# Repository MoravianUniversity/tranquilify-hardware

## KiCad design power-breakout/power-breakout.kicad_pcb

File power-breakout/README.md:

# Power Breakout

Battery + USB-C power path breakout for Tranquilify. Supplies switched **+3.3 V** to an ESP32-P4 (and onboard C6), two ADAU1787 codec boards, with charge-while-off, ship mode, and I2C fuel gauging.

Schematic-first; PCB later. Target assembly: JLCPCB.

## Role in the system

| Consumer | Rail | Notes |
|----------|------|--------|
| ESP32-P4 + ESP32-C6 | `+3V3` (switched) | Soft power via buck EN / host `HOST_3V3_EN` |
| 2× ADAU1787 breakouts | `+3V3` | Codecs make their own 1.8 V on-board |
| STC3115 fuel gauge | Battery (always) | Low-side sense; I2C @ 0x38 on host bus |
| Soft-power + charger | Always-on from `SYS` / pack | Charge LED works while “off”; soft-power is off-board via J6 |

## Locked requirements

- **USB-C** 5 V sink only; **USB HS** D+/D− shared with charger BC1.2 via DSEL mux
- **Power path:** system runs from USB with empty or **missing** battery
- **Battery:** ~3500 mAh 1S Li-ion target (was Adafruit 353 6600 mAh), JST-PH, pack PCM, **no NTC**
- Charge ~**1 A** (pack max 1.5 A; ICHG in firmware + ILIM pin)
- Soft power = **Mode B** (cut system load / Waveshare 3V3_EN); path toward deep-sleep later
- Soft-power UX (hold-to-on, no auto-on on plug-in, click/hold to host) is **off-board** on **J6 SPWR** — not populated on this rev
- Critical-battery auto-off via gauge + firmware (once soft-power can cut `BUCK_EN`)
- Ship mode via BQ25895 `BATFET_DIS` / `/QON` wake
- Connectors: JST-PH battery; JST-GH for power, control, USB data; 1.27 mm header for soft-power experiments

## Architecture

```
USB-C VBUS ──► BQ25895 (power path, ~1 A charge)
                 │
    D+/D− ──► FSUSB42 (DSEL) ──┬── CHG_DP/DN → BQ25895 BC1.2
                               └── HOST_DP/DN → J2 USB header
                 │
    PACK+ ◄──────┤◄── JST-PH pin1; charger BAT = PACK+
                 │
                SYS
                 │
   ┌─────────────┼──────────────────┐
   │             │                  │
always-on   R16 100k ↑ EN      STAT → CHG LED
(SYS)            │
                 ▼
         TPS62823 EN → +3V3 → P4 / C6 / codecs
                 │
         J1 POWER: GND / HOST_3V3_EN (OD) / +3V3

    PACK- (JST-PH pin2) ── 10 mΩ R9 ──► GND   (STC3115 CG/GND Kelvin)

J6 SPWR: SYS / GND / BTN / BUCK_EN
  BTN also → BQ25895 /QON (ship wake)
  Empty header ⇒ EN pulled up ⇒ +3V3 default on when SYS is up
STC3115 low-side sense on PACK-, I2C @ 0x38 (host bus, not codec bus)
```

RGB indicator lives on the eventual main board, not this power breakout.

**Dropped vs earlier draft:** no LM66200 / `AUX_5V` input OR. USB-C is the only VBUS source into the charger. On-board **MAX16150** soft-power IC removed in favor of **J6 SPWR** (see below).

### Soft power vs ship mode

| State | What happens |
|-------|----------------|
| **Default (no SPWR board)** | `BUCK_EN` pulled to `SYS` via R16 → `+3V3` on whenever `SYS` exists (USB and/or battery). |
| **User off (with SPWR daughter)** | Daughter deasserts `BUCK_EN` → `+3V3` down. Charger + gauge live. USB can still charge. |
| **Ship** | Host I2C → BQ25895 `BATFET_DIS`; BATFET off; ~µA. Exit: long `/QON` (BTN to GND) or USB plug. |
| **Deep sleep (later)** | Keep `+3V3` up; P4 sleep — optional future |

### Soft-power experiment port (J6 SPWR)

No on-board pushbutton controller. **J6** (1×4, 1.27 mm) exposes the always-on domain so you can try options without a power-board respin:

| Pin | Net | Contract |
|-----|-----|----------|
| 1 | `SYS` | Always-on supply for a soft-power circuit |
| 2 | `GND` | Ground |
| 3 | `BTN` | Active-low button node; also tied to BQ25895 `/QON` |
| 4 | `BUCK_EN` | TPS62823 `EN` (active high). Weak **100 kΩ** pull-up to `SYS` (R16) for default-on |

**Suggested implementations on J6**

- **MAX16150** (or similar): VCC=`SYS`, PB_IN=`BTN`, OUT→`BUCK_EN`, CLR/INT to the host as needed (host wires are no longer on J3).
- **Simpler:** discrete latch / open-drain MOSFET from a GPIO daughterboard; OD **low** on `BUCK_EN` for off.
- **Bring-up:** leave J6 open — rail stays on; short `BTN`–`GND` only if testing `/QON` / ship wake.

Product UX (hold-to-on, no auto-on on plug-in, click vs hold) lives entirely on whatever you plug into SPWR (+ host wiring you add).

### Dev board (Waveshare ESP32-P4-WIFI6)

| Mode | Intent |
|------|--------|
| **B – Rail / 3V3_EN** | Feed Waveshare from `+3V3`; `HOST_3V3_EN` OD-low while breakout `SYS` is present (disables module regulator when breakout is powering the rail). |
| USB data | Host USB via J2 (`HOST_DP`/`HOST_DN`); pin 1 V left N/C. DSEL mux hands D+/D− to host after BC1.2. |

## Major parts (schematic)

| Ref | Part | Why |
|-----|------|-----|
| U1 | **BQ25895RTW** | Switch-mode power-path charger, ship (`BATFET_DIS`), `/QON` wake, `STAT` LED, DSEL, I2C; ICHG ~1 A in firmware |
| U3 | **STC3115AIQT** | OptimGauge mixed mode; ~3500 mAh; low-side 10 mΩ; LCSC C2688637. `ALM`→`BAT_ALM` (RN1 pull-up); `RSTIO`→GND (feature off); `BATD` 1 kΩ→GND; VIN filter R11+C16; VCC C10 1 µF |
| U4 | **TPS62823DLC** | 3 A buck, VIN down to 2.4 V → `+3V3`; `EN` default-on via R16 |
| U5 | **USBLC6-2SC6** | USB ESD on `USB_DP`/`USB_DN` |
| U6 | **FSUSB42MUX** | DSEL mux: BC1.2 (HSD1) vs host USB (HSD2); OE# grounded; VCC from `SYS` |
| R16 | **100 kΩ** | `SYS` → `BUCK_EN` pull-up (default on) |
| D1 | LED + R from `STAT` | Charge LED while system off |
| J1 | JST-GH 3 POWER | `GND` / `HOST_3V3_EN` / `+3V3` |
| J2 | JST-GH 4 USB_HDR | USB data header: V N/C, D−, D+, GND |
| J3 | JST-GH 5 CONTROL | I2C + `CHG_INT` + `BAT_ALM` |
| J4 | USB-C + 5.1 kΩ CC | 5 V sink; D+/D− to ESD + mux |
| J5 | JST-PH 2-pin BAT | Battery (`PACK+` / `PACK-`) |
| J6 | 1×4 1.27 mm SPWR | Soft-power experiment: `SYS` / `GND` / `BTN` / `BUCK_EN` |

**FW notes:** clear `MAXC_EN` + `HVDCP_EN` so DSEL releases after BC1.2; set ICHG/VREG; disable or pet charger WDT.

## Datasheets

Saved under `../datasheets/`:

| File | Part |
|------|------|
| `BQ25895_datasheet.pdf` | Charger |
| `BQ25628_datasheet.pdf` | Alternate charger (no D+/D−; not used) |
| `MAX16150_datasheet.pdf` | Soft-power pushbutton IC (optional on J6; not on board) |
| `STC3115_datasheet.pdf` | Fuel gauge (STC3115AIQT) |
| `AN4324_STC3115_system_integration.pdf` | STC3115 integration (if present) |
| `TPS62823_datasheet.pdf` | 3.3 V buck |
| `LM66200_datasheet.pdf` | Dual ideal diode (not used on this rev) |
| `LM66100_datasheet.pdf` | Prior single ideal diode (not used) |
| `ESP32-P4-WIFI6-datasheet.pdf` | Waveshare host module |

## Host connectors

### J1 POWER (JST GH-3)

| Pin | Net | Notes |
|-----|-----|--------|
| 1 | `GND` | |
| 2 | `HOST_3V3_EN` | OD low while `SYS` present; floats when breakout unpowered |
| 3 | `+3V3` | Switched 3.3 V out |

### J2 USB_HDR (JST GH-4)

| Pin | Net | Notes |
|-----|-----|--------|
| 1 | — | V left N/C (host supplies USB VBUS separately if needed) |
| 2 | `HOST_DN` | From mux HSD2 |
| 3 | `HOST_DP` | |
| 4 | `GND` | |

### J3 CONTROL (JST GH-5)

| Pin | Net | Notes |
|-----|-----|--------|
| 1 | `GND` | |
| 2 | `SCL` | 3.3 V I2C (charger `0x6A`; gauge **0x38**) |
| 3 | `SDA` | |
| 4 | `CHG_INT` | BQ25895 `/INT` (OD; RN1 10 kΩ to `+3V3`) |
| 5 | `BAT_ALM` | STC3115 `ALM` (OD; RN1 10 kΩ to `+3V3`) |

### J6 SPWR (1×4, 1.27 mm)

| Pin | Net | Notes |
|-----|-----|--------|
| 1 | `SYS` | Always-on |
| 2 | `GND` | |
| 3 | `BTN` | Shared with `/QON` |
| 4 | `BUCK_EN` | Active-high enable; pulled up on board |

Also: `J4` USB-C, `J5` battery (PH, pin1=`PACK+`, pin2=`PACK-` via R9 to GND).

Host wiring detail: `HOST-SETUP.md`.

## Non-goals (this board)

- Codec 1.8 V generation (on ADAU1787 breakouts)
- RGB LED (on eventual main board)
- On-board soft-power IC / dedicated button jack (use J6)
- Battery NTC (pack has none; TS biased for “OK”)
- AUX 5 V input / ideal-diode OR (dropped this rev)

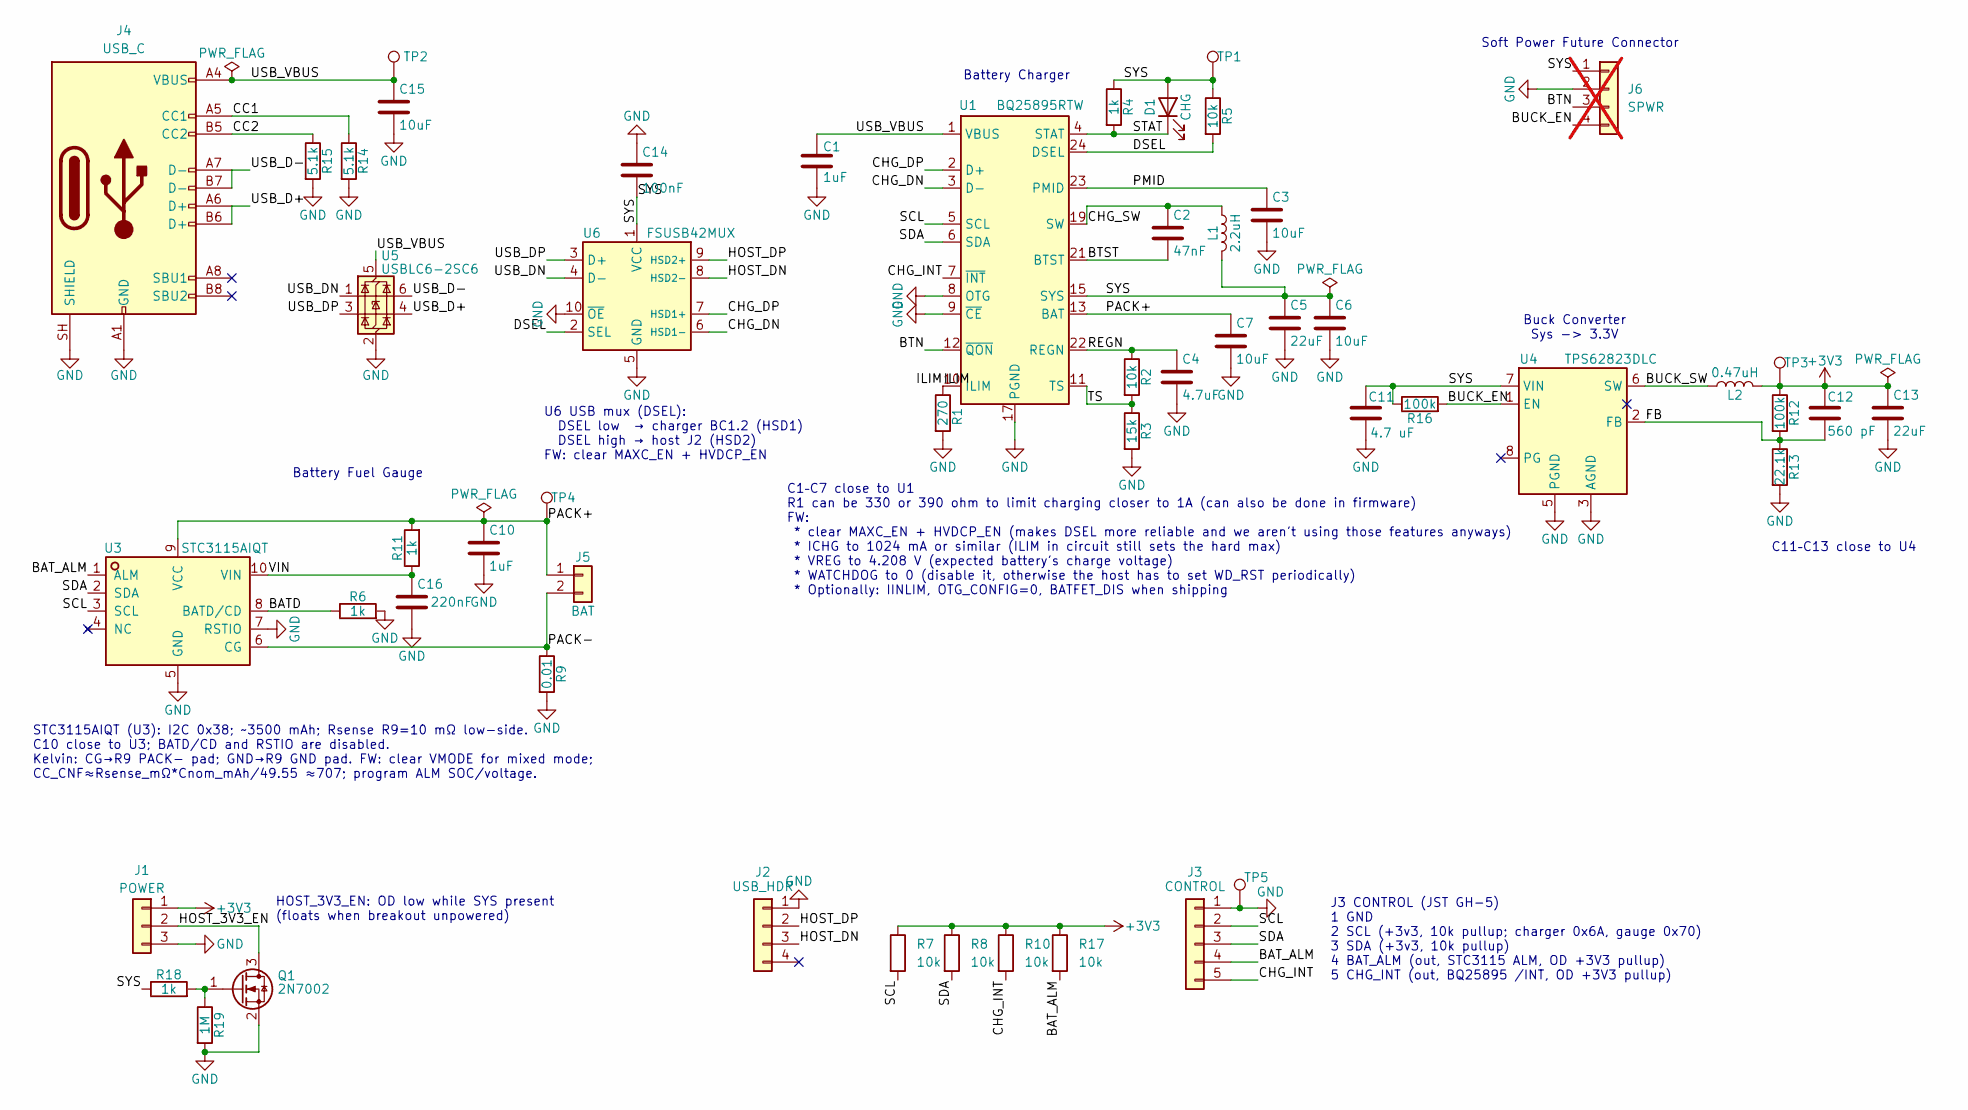
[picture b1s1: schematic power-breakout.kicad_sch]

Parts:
C1: 1uF; C_0402_1005Metric; JLCPCB Item # C49210445
C2: 47nF; C_0402_1005Metric; JLCPCB Item # C272875
C3, C6, C7: 10uF; C_0805_2012Metric; JLCPCB Item # C95841
C4: 4.7uF; C_0603_1608Metric; JLCPCB Item # C19666
C5: 22uF; C_1206_3216Metric; JLCPCB Item # C5252682
C10: 1uF; C_0603_1608Metric; JLCPCB Item # C95843
C11: 4.7 uF; C_0603_1608Metric; JLCPCB Item # C18185770
C12: 560 pF; C_0603_1608Metric; JLCPCB Item # C107054
C13: 22uF; C_0805_2012Metric; JLCPCB Item # C53133025
C14: 100nF; C_0603_1608Metric; JLCPCB Item # C36911391
C15: 10uF; C_1206_3216Metric; JLCPCB Item # C14860
C16: 220nF; C_0603_1608Metric; JLCPCB Item # C1595
D1: CHG; LED_0603_1608Metric; JLCPCB Item # C2892759
J1: POWER; JST_GH_SM03B-GHS-TB_1x03-1MP_P1.25mm_Horizontal; JLCPCB Item # C514175
J2: USB_HDR; JST_GH_SM04B-GHS-TB_1x04-1MP_P1.25mm_Horizontal; JLCPCB Item # C189895
J3: CONTROL; JST_GH_SM05B-GHS-TB_1x05-1MP_P1.25mm_Horizontal; JLCPCB Item # C189896
J4: USB_C; USB_C_Receptacle_HRO_TYPE-C-31-M-12; JLCPCB Item # C165948
J5: BAT; JST_PH_B2B-PH-K_1x02_P2.00mm_Vertical; JLCPCB Item # C131337
J6: SPWR; PinHeader_1x04_P1.27mm_Vertical; not fitted
L1: 2.2uH; L_1008_2520Metric; JLCPCB Item # C1017131
L2: 0.47uH; L_1008_2520Metric; JLCPCB Item # C24296304
Q1: 2N7002; SOT-23; JLCPCB Item # C8545
R1: 270; R_0603_1608Metric; JLCPCB Item # C22966
R2, R5: 10k; R_0603_1608Metric; JLCPCB Item # C25804
R3: 15k; R_0603_1608Metric; JLCPCB Item # C22809
R4, R6, R11, R18: 1k; R_0603_1608Metric; JLCPCB Item # C21190
R7, R8, R10, R17: 10k; R_0402_1005Metric; JLCPCB Item # C25744
R9: 0.01; R_1206_3216Metric; JLCPCB Item # C7467248
R12: 100k; R_0603_1608Metric; JLCPCB Item # C25803
R13: 22.1k; R_0603_1608Metric; JLCPCB Item # C137768
R14, R15: 5.1k; R_0603_1608Metric; JLCPCB Item # C23186
R16: 100k; R_0402_1005Metric; JLCPCB Item # C25741
R19: 1M; R_0603_1608Metric; JLCPCB Item # C22935
TP1, TP2, TP3, TP4, TP5: TestPoint; TestPoint_Pad_D1.0mm
U1: BQ25895RTW; Texas_RTW_WQFN-24-1EP_4x4mm_P0.5mm_EP2.7x2.7mm_ThermalVias; JLCPCB Item # C80200
U3: STC3115AIQT; ST_UFDFPN-10_2x3mm_P0.5mm; JLCPCB Item # C2688637
U4: TPS62823DLC; Texas_VSON-HR-8_1.5x2mm_P0.5mm; JLCPCB Item # C2693497
U5: USBLC6-2SC6; SOT-23-6; JLCPCB Item # C2827654
U6: FSUSB42MUX; MSOP-10_3x3mm_P0.5mm; JLCPCB Item # C11355

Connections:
+3V3: C12.1, C13.1, J1.1, L2.2, R7.1, R8.1, R10.1, R12.1, R17.1, TP3.1 (1_1)
/BATD: R6.1, U3.8 (BATD/CD)
/BAT_ALM: J3.4, R17.2, U3.1 (ALM)
/BTN: J6.3, U1.12 (~QON)
/BTST: C2.2, U1.21 (BTST)
/BUCK_EN: J6.4, R16.2, U4.1 (EN)
/BUCK_SW: L2.1, U4.6 (SW)
/CC1: J4.A5 (CC1), R14.1
/CC2: J4.B5 (CC2), R15.1
/CHG_DN: U1.3 (D-), U6.6 (HSD1-)
/CHG_DP: U1.2 (D+), U6.7 (HSD1+)
/CHG_INT: J3.5, R10.2, U1.7 (~INT)
/CHG_SW: C2.1, L1.1, U1.19 (SW), U1.20 (SW)
/DSEL: R5.2, U1.24 (DSEL), U6.2 (SEL)
/FB: C12.2, R12.2, R13.1, U4.2 (FB)
/HOST_3V3_EN: J1.2, Q1.3 (D)
/HOST_DN: J2.3, U6.8 (HSD2-)
/HOST_DP: J2.2, U6.9 (HSD2+)
/ILIM: R1.1, U1.10 (ILIM)
/PACK+: C7.1, C10.1, J5.1, R11.2, TP4.1 (1_1), U1.13 (BAT), U1.14 (BAT), U3.9 (VCC)
/PACK-: J5.2, R9.1, U3.6 (CG)
/PMID: C3.1, U1.23 (PMID)
/REGN: C4.1, R2.1, U1.22 (REGN)
/SCL: J3.2, R7.2, U1.5 (SCL), U3.3 (SCL)
/SDA: J3.3, R8.2, U1.6 (SDA), U3.2 (SDA)
/STAT: D1.1 (K), R4.2, U1.4 (STAT)
/SYS: C5.1, C6.1, C11.1, C14.2, D1.2 (A), J6.1, L1.2, R4.1, R5.1, R16.1, R18.1, TP1.1 (1_1), U1.15 (SYS), U1.16 (SYS), U4.7 (VIN), U6.1 (VCC)
/TS: R2.2, R3.1, U1.11 (TS)
/USB_D+: J4.A6 (D+), J4.B6 (D+), U5.4 (I/O2)
/USB_D-: J4.A7 (D-), J4.B7 (D-), U5.6 (I/O1)
/USB_DN: U5.1 (I/O1), U6.4 (D-)
/USB_DP: U5.3 (I/O2), U6.3 (D+)
/USB_VBUS: C1.1, C15.1, J4.A4 (VBUS), J4.A9 (VBUS), J4.B4 (VBUS), J4.B9 (VBUS), TP2.1 (1_1), U1.1 (VBUS), U5.5 (VBUS)
/VIN: C16.1, R11.1, U3.10 (VIN)
GND: C1.2, C3.2, C4.2, C5.2, C6.2, C7.2, C10.2, C11.2, C13.2, C14.1, C15.2, C16.2, J1.3, J2.1, J3.1, J4.A1 (GND), J4.A12 (GND), J4.B1 (GND), J4.B12 (GND), J4.SH (SHIELD), J6.2, Q1.2 (S), R1.2, R3.2, R6.2, R9.2, R13.2, R14.2, R15.2, R19.2, TP5.1 (1_1), U1.8 (OTG), U1.9 (~CE), U1.17 (PGND), U1.18 (PGND), U1.25 (PGND), U3.5 (GND), U3.7 (RSTIO), U4.3 (AGND), U4.5 (PGND), U5.2 (GND), U6.5 (GND), U6.10 (~OE)
unnamed: Q1.1 (G), R18.2, R19.1

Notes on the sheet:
HOST_3V3_EN: OD low while SYS present (floats when breakout unpowered)
C1–C7 close to U1 R1 can be 330 or 390 ohm to limit charging closer to 1A (can also be done in firmware) FW: * clear MAXC_EN + HVDCP_EN (makes DSEL more reliable and we aren't using those features anyways) * ICHG to 1024 mA or similar (ILIM in circuit still sets the hard max) * VREG to 4.208 V (exp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
C11–C13 close to U4
Battery Fuel Gauge
STC3115AIQT (U3): I2C 0x38; ~3500 mAh; Rsense R9=10 mΩ low-side. C10 close to U3; BATD/CD and RSTIO are disabled. Kelvin: CG→R9 PACK- pad; GND→R9 GND pad. FW: clear VMODE for mixed mode; CC_CNF≈Rsense_mΩ*Cnom_mAh/49.55 ≈707; program ALM SOC/voltage.
U6 USB mux (DSEL): DSEL low → charger BC1.2 (HSD1) DSEL high → host J2 (HSD2) FW: clear MAXC_EN + HVDCP_EN
Battery Charger
J3 CONTROL (JST GH-5) 1 GND 2 SCL (+3v3, 10k pullup; charger 0x6A, gauge 0x70) 3 SDA (+3v3, 10k pullup) 4 BAT_ALM (out, STC3115 ALM, OD +3V3 pullup) 5 CHG_INT (out, BQ25895 /INT, OD +3V3 pullup)
Soft Power Future Connector
Buck Converter Sys -> 3.3V

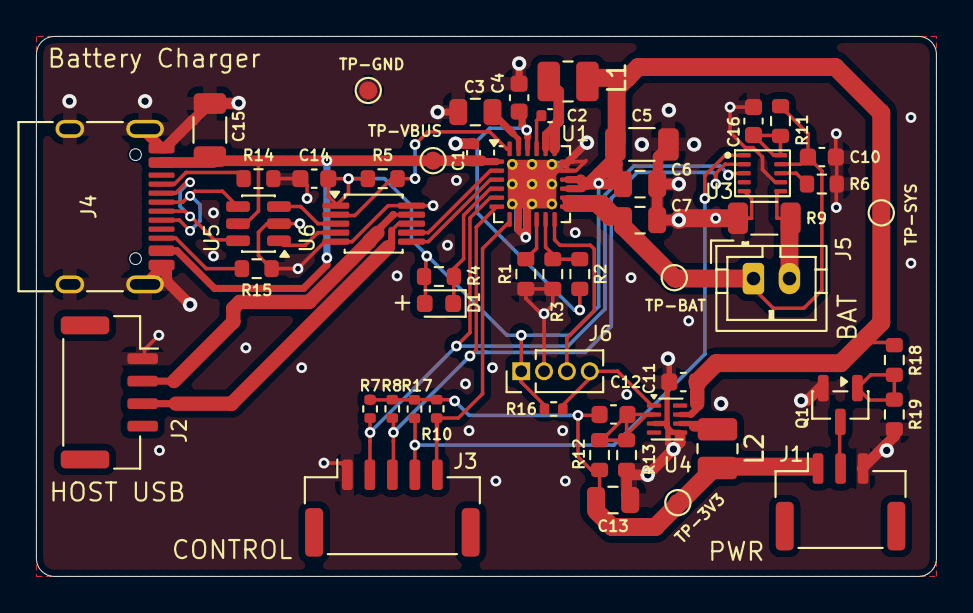
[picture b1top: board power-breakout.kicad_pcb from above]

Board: 2 copper layers, 50.0 x 30.0 mm, 53 parts (0 on the bottom side), 36 nets.

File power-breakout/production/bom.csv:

Designator,Footprint,Quantity,Value,LCSC Part #
C1,0402,1,1uF,C49210445
C10,0603,1,1uF,C95843
C11,0603,1,4.7 uF,C18185770
C12,0603,1,560 pF,C107054
C13,0805,1,22uF,C53133025
C14,0603,1,100nF,C36911391
C15,1206,1,10uF,C14860
C16,0603,1,220nF,C1595
C2,0402,1,47nF,C272875
"C3, C6, C7",0805,3,10uF,C95841
C4,0603,1,4.7uF,C19666
C5,1206,1,22uF,C5252682
D1,0603,1,CHG,C2892759
J1,JST_GH_SM03B-GHS-TB_1x03-1MP_P1.25mm_Horizontal,1,POWER,C514175
J2,JST_GH_SM04B-GHS-TB_1x04-1MP_P1.25mm_Horizontal,1,USB_HDR,C189895
J3,JST_GH_SM05B-GHS-TB_1x05-1MP_P1.25mm_Horizontal,1,CONTROL,C495552
J4,USB_C_Receptacle_HRO_TYPE-C-31-M-12,1,USB_C,C165948
J5,JST_PH_B2B-PH-K_1x02_P2.00mm_Vertical,1,BAT,C131337
L1,1008,1,2.2uH,C1017131
L2,1008,1,0.47uH,C24296304
Q1,SOT-23,1,2N7002,C8545
R1,0603,1,270,C22966
"R10, R17, R7, R8",0402,4,10k,C25744
"R11, R18, R4, R6",0603,4,1k,C21190
R12,0603,1,100k,C25803
R13,0603,1,22.1k,C137768
"R14, R15",0603,2,5.1k,C23186
R16,0402,1,100k,C25741
R19,0603,1,1M,C22935
"R2, R5",0603,2,10k,C25804
R3,0603,1,15k,C22809
R9,1206,1,0.01,C7467248
"TP1, TP2, TP3, TP4, TP5",TestPoint_Pad_D1.0mm,5,TestPoint,
U1,Texas_RTW_WQFN-24-1EP_4x4mm_P0.5mm_EP2.7x2.7mm_ThermalVias,1,BQ25895RTW,C80200
U3,ST_UFDFPN-10_2x3mm_P0.5mm,1,STC3115AIQT,C2688637
U4,Texas_VSON-HR-8_1.5x2mm_P0.5mm,1,TPS62823DLC,C2693497
U5,SOT-23-6,1,USBLC6-2SC6,C2827654
U6,MSOP-10_3x3mm_P0.5mm,1,FSUSB42MUX,C11355

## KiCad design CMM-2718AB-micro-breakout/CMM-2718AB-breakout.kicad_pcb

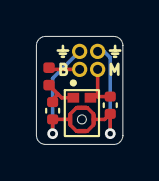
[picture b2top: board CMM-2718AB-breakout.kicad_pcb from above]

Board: 2 copper layers, 4.8 x 6.0 mm, 5 parts (0 on the bottom side), 4 nets.

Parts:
C1: 100nF; C_0402_1005Metric
C2: 15pF; C_0402_1005Metric
FB1: BLM15AG102SN1D; L_0402_1005Metric
J1: Conn; PinHeader_2x02_P1.00mm_Vertical
U1: CMM-2718AB-38164W-TR

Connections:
/BIAS: FB1.1, J1.3
/OUT: C2.1, J1.4, U1.2 (OUT)
/VDD: C1.1, FB1.2, U1.1 (VDD)
GND: C1.2, C2.2, J1.1, J1.2, U1.3 (GND)

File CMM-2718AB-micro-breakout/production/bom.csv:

Designator,Footprint,Quantity,Value,LCSC Part #
"BOARD_0-C1, BOARD_1-C1",0603,2,100nF,C108079
"BOARD_0-C2, BOARD_1-C2",0603,2,15pF,C107037
"BOARD_0-FB1, BOARD_0-FB2, BOARD_1-FB1, BOARD_1-FB2",0603,4,BLM18AG102SN1D,C85824
"BOARD_0-U1, BOARD_1-U1",CMM-2718AB-38164W-TR,2,CMM-2718AB-38164W-TR,C7497787
"BOARD_2-C1, BOARD_3-C1",0402,2,100nF,
"BOARD_2-C2, BOARD_3-C2",0402,2,15pF,
"BOARD_2-FB1, BOARD_3-FB1",0402,2,BLM15AG102SN1D,
"BOARD_2-U1, BOARD_3-U1",CMM-2718AB-38164W-TR,2,CMM-2718AB-38164W-TR,

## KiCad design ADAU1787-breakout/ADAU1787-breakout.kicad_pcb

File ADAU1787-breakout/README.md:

# ADAU1787 Breakout

Compact breakout for the **Analog Devices ADAU1787BCBZ** (WLCSP-42) codec / ANC DSP. Intended for Tranquilify ear-cup prototyping and the first product batch: one board per ear, driven by a **3.3 V power / 1.8 V logic** host (target: ESP32-P4).

## Role in the system

| Ear path | Mic board | ADAU connector | Notes |
|----------|-----------|----------------|--------|
| Feedforward (FF) | `CMM-2718AB-breakout` (11.5×13.5 mm) | **J5** | Outer / ambient mic |
| Feedback (FB) | `CMM-2718AB-micro-breakout` (4.8×6 mm) | **J3** | In-ear mic + speaker on same cable |
| Optional extra mics | header wiring | **J6** | MIC1 / MIC3; leave unpopulated if unused |
| Host | ESP32-P4 (or equivalent) | **J1** | I2C + I2S + PD_N + 3.3 V |

Typical cable into an earbud (see `Earbud Design Notes.md`): driver pair, FB mic OUT/GND, FB mic BIAS/GND — the micro breakout and speaker sit in the bud; the FF mic breakout is the larger board.

## Codec (U1)

| Item | Value |
|------|--------|
| Part | ADAU1787BCBZ |
| Package | WLCSP-42, 0.35 mm pitch (`lib/…/WLCSP-42_…`) |
| Analog / HP / IO / REG_EN | **+1.8 V** from on-board LDO |
| Host supply into board | **+3.3 V** only (on J1) |
| Digital I/O | **1.8 V logic — not 3.3 V tolerant** |
| Clock | On-board 24.576 MHz crystal (no external MCLK) |

Datasheets (repo): `../datasheets/ADAU1787_datasheet_RevA.pdf`, `../datasheets/EVAL-ADAU1787Z-UG-1532.pdf`

## Power

```
J1 +3V3 ── FB1 ── LDO_IN ── U2 TLV75518 ── +1V8
                              │
                    C20 (1µF), C22 (10µF) on input side
                    C21 (2.2µF) + local 100nF / 10µF on +1V8
```

- **U2** (`TLV75518PDBV`, SOT-23-5) generates +1.8 V for AVDD, HPVDD, IOVDD, and REG_EN.
- **FB1**: 600 Ω @ 100 MHz / 1 A class ferrite on the 3.3 V → LDO input path.
- I2C pull-ups **R1 / R2** (4.7 kΩ) are to **+1.8 V**. Remove them if the host already provides 1.8 V pull-ups.
- **SELFBOOT** is held low by R5 (10 kΩ) — no EEPROM self-boot.
- **PD_N** is pulled high by R6 (10 kΩ); host may drive it low to power down.

## I2C address straps (per ear)

Hard-wired with the on-board **ADDR0 / ADDR1** 0603 selectors (`A0` / `A1`). Populate **one** 10 kΩ per bit:

| Strap | LO (0) | HI (1) |
|-------|--------|--------|
| Meaning | 10 kΩ to **GND** | 10 kΩ to **+1.8 V** |

| Ear | ADDR1 | ADDR0 | 7-bit address |
|-----|-------|-------|---------------|
| **Right** | 0 (LO) | 0 (LO) | **0x28** |
| **Left** | 1 (HI) | 0 (LO) | **0x2A** |

Full map on the schematic sheet: 0x28 / 0x29 / 0x2A / 0x2B for ADDR1:ADDR0 = 00 / 01 / 10 / 11.

## Connectors

### J1 — HOST_IF (JST GH 12-pin)

`JST_GH_SM12B-GHS-TB`, 1.25 mm pitch, horizontal.

| Pin | Net | Function |
|-----|-----|----------|
| 1 | SCL | I2C clock (1.8 V) |
| 2 | SDA | I2C data (1.8 V) |
| 3 | BCLK_0 | I2S bit clock |
| 4 | GND | |
| 5 | FSYNC_0 | I2S frame sync / LRCLK |
| 6 | GND | |
| 7 | SDATAO_0_J | I2S data out (via R18 47 Ω) |
| 8 | SDATAI_0 | I2S data in |
| 9 | GND | |
| 10 | PD_N | Active-low power-down |
| 11 | GND | |
| 12 | +3V3 | Board supply |

### J3 — FB_MIC_SPK (feedback mic + in-ear speaker)

`JST_GH_SM06B-GHS-TB`, 6-pin. Feedback (in-ear) mic on the **micro** CMM breakout, plus headphone / receiver drive.

| Pin | Net | Function |
|-----|-----|----------|
| 1 | HPOUTP0 | Speaker / HP positive (after optional R19) |
| 2 | HPOUTN0 | Speaker / HP negative (after optional R20) |
| 3 | GND | |
| 4 | MIC2_IN | Feedback mic OUT (AC-coupled on board → AIN2) |
| 5 | GND | |
| 6 | MICBIAS0 | Bias for feedback mic |

### J5 — FF_MIC (feedforward mic)

`JST_GH_SM04B-GHS-TB`, 4-pin. Feedforward mic on the **regular** CMM breakout.

| Pin | Net | Function |
|-----|-----|----------|
| 1 | GND | |
| 2 | MIC0_IN | FF mic OUT (AC-coupled on board → AIN0) |
| 3 | GND | |
| 4 | MICBIAS1 | Bias for FF mic |

### J6 — MIC1_MIC3_HDR (optional)

2×3 pin header, 2.00 mm. Extra analog mic inputs; leave unpopulated when unused.

| Pin | Net |
|-----|-----|
| 1 | MIC1_IN |
| 2 | GND |
| 3 | MICBIAS1 |
| 4 | GND |
| 5 | MIC3_IN |
| 6 | GND |

## Analog mic inputs

Each used AIN path has:

- Series **4.7 µF X7R 10% 16V** (0805) AC-coupling: C17→AIN0, C16→AIN2, C18→AIN1, C19→AIN3
- **49.9 kΩ** to GND on the mic side of the coupling cap (R8 / R7 / R9 / R10)

MICBIAS0 / MICBIAS1 each have **1 µF** local bypass (C12 / C13). CM filter: C10 10 µF + C11 100 nF.

## Headphone / speaker path (HPOUT0)

Default path is through **R19 / R20** (`0R / ferrite` placeholders) to HPOUTP0 / HPOUTN0 on J3.

Optional tuning (populate only if needed):

| Ref | Value field | Role |
|-----|-------------|------|
| R19, R20 | `0R / ferrite` | Series 0 Ω jumpers or ferrites on HP outs |
| C23, C24 | `Shunt N` / `Shunt P` | Optional shunts to GND |
| R23 | `P-N` | Optional P–N damping / load between HP outs |

Treat these as **DNP by default** unless a speaker loadout needs them.

## Clock

| Ref | Part / value | Notes |
|-----|--------------|--------|
| Y1 | SX32Y024576DC1T001 | 24.576 MHz, CL = 12 pF |
| C14, C15 | 18 pF | Load caps |

## Digital / unused pins

Unused digital pins (second I2S port, DMIC clocks/data, etc.) are left unconnected. Enable the codec’s **internal pull-downs** in firmware on input-capable unused pins (schematic note calls out BCLK_1, FSYNC_1, SDATAI_1, SDATAO_1, DMIC_CLK0/1 and related).

SDATAO_0 goes through **R18** (47 Ω) to the host connector.

## Mechanical / PCB

| Item | Value |
|------|--------|
| Board size | **~27.3 × 34.5 mm** |
| Layers | **4** |
| Fab target | JLCPCB-class; via-in-pad allowed for U1 WLCSP |
| Libraries | Project-local `lib/ADAU1787-breakout.*` |

## Firmware / host checklist

1. Supply **3.3 V** on J1 pin 12; keep digital lines at **1.8 V**.
2. Strap addresses: right **0x28**, left **0x2A** (see table above).
3. Bring up I2C, release PD_N, configure PLL from the 24.576 MHz crystal.
4. Enable internal pull-downs on unused digital inputs.
5. Route FF mic → J5, FB mic + speaker → J3; bias rails must stay within the mic’s 1.5–3.6 V VDD range (codec MICBIAS settings).

## Project files

| Path | Role |
|------|------|
| `ADAU1787-breakout.kicad_pro` | KiCad project |
| `ADAU1787-breakout.kicad_sch` | Schematic |
| `ADAU1787-breakout.kicad_pcb` | PCB |
| `docs/schematic.png` | Schematic render |
| `docs/board.png` / `docs/board-3d.png` | Board renders |
| `lib/ADAU1787-breakout.kicad_sym` | Codec symbol |
| `lib/ADAU1787-breakout.pretty/` | WLCSP + selector footprints |

## Related boards

- [`CMM-2718AB-breakout`](../CMM-2718AB-breakout/README.md) — FF mic (this board’s J5)
- `CMM-2718AB-micro-breakout` — FB mic in the earbud (this board’s J3); see that folder’s `ORDERING.md`

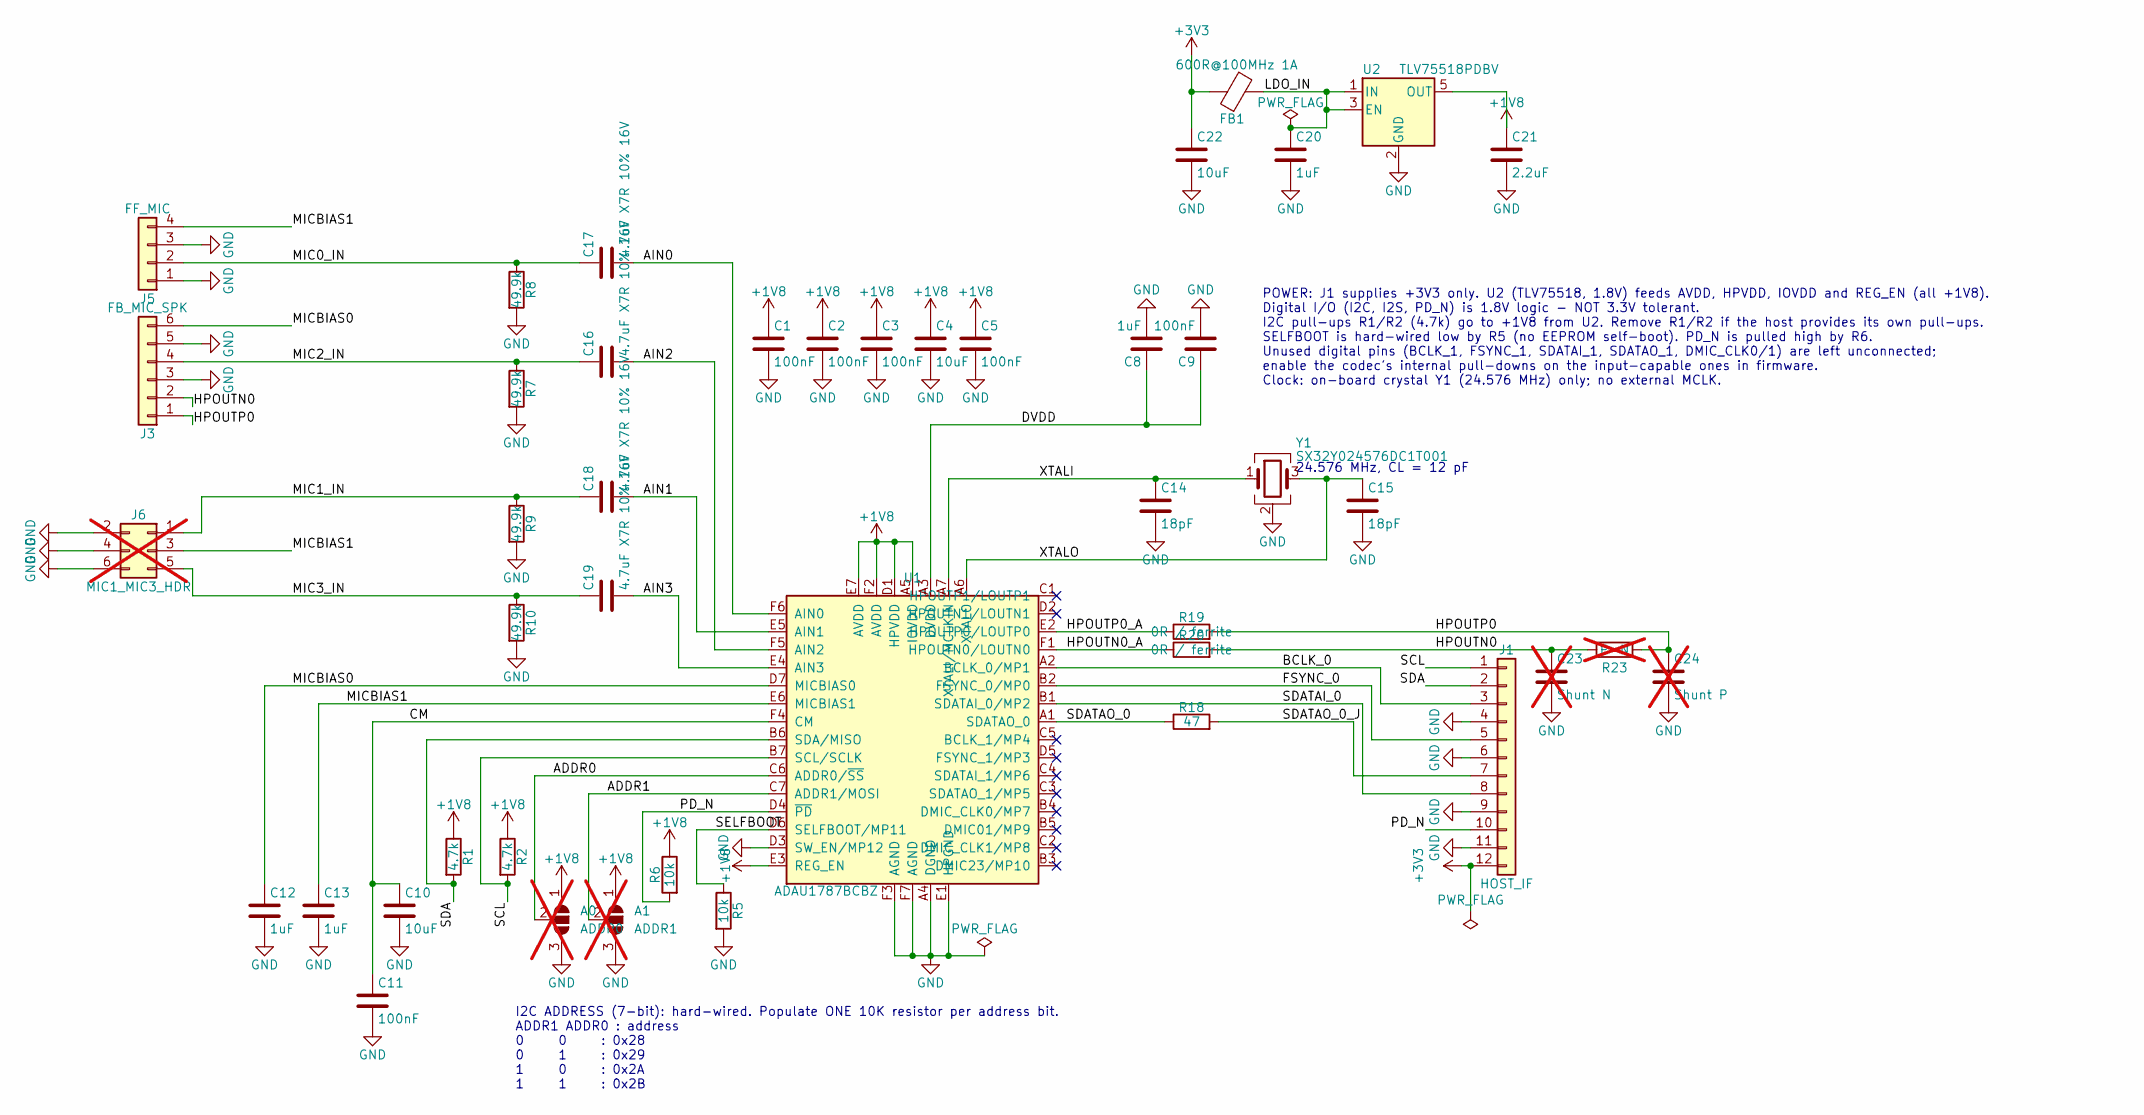
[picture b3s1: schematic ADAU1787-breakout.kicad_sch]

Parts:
A0: ADDR0; 0603_selector; not fitted
A1: ADDR1; 0603_selector; not fitted
C1, C2, C3, C5, C9, C11: 100nF; C_0402_1005Metric; JLCPCB Part # C1525
C4, C10, C22: 10uF; C_0603_1608Metric; JLCPCB Part # C2959727
C8, C12, C13, C20: 1uF; C_0402_1005Metric; JLCPCB Part # C49210445
C14, C15: 18pF; C_0402_1005Metric; JLCPCB Part # C1549
C16, C17, C18, C19: 4.7uF X7R 10% 16V; C_0805_2012Metric; JLCPCB Part # CL21B475KOFNNNE
C21: 2.2uF; C_0402_1005Metric; JLCPCB Part # C2997286
C23: Shunt N; C_0603_1608Metric_Pad1.08x0.95mm_HandSolder; not fitted
C24: Shunt P; C_0603_1608Metric_Pad1.08x0.95mm_HandSolder; not fitted
FB1: 600R@100MHz 1A; L_0603_1608Metric; JLCPCB Part # C108301
J1: HOST_IF; JST_GH_SM12B-GHS-TB_1x12-1MP_P1.25mm_Horizontal; JLCPCB Part # C265421
J3: FB_MIC_SPK; JST_GH_SM06B-GHS-TB_1x06-1MP_P1.25mm_Horizontal; JLCPCB Part # C133065
J5: FF_MIC; JST_GH_SM04B-GHS-TB_1x04-1MP_P1.25mm_Horizontal; JLCPCB Part # C189895
J6: MIC1_MIC3_HDR; PinHeader_2x03_P2.00mm_Vertical; not fitted
R1, R2: 4.7k; R_0402_1005Metric; JLCPCB Part # C25900
R5, R6: 10k; R_0402_1005Metric; JLCPCB Part # C25744
R7, R8, R9, R10: 49.9k; R_0402_1005Metric; JLCPCB Part # C25897
R18: 47; R_0402_1005Metric; JLCPCB Part # C25118
R19, R20: 0R / ferrite; R_0603_1608Metric_Pad0.98x0.95mm_HandSolder; JLCPCB Part # C21189
R23: P-N; R_0603_1608Metric_Pad0.98x0.95mm_HandSolder; not fitted
U1: ADAU1787BCBZ; WLCSP-42_2.695x2.320mm_P0.35mm; JLCPCB Part # C3226201
U2: TLV75518PDBV; SOT-23-5; JLCPCB Part # C2877863
Y1: SX32Y024576DC1T001; Crystal_SMD_3225-4Pin_3.2x2.5mm; JLCPCB Part # C20612976

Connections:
+1V8: A0.1 (A), A1.1 (A), C1.1, C2.1, C3.1, C4.1, C5.1, C21.1, R1.1, R2.1, R6.1, U1.A5 (IOVDD), U1.D1 (HPVDD), U1.E3 (REG_EN), U1.E7 (AVDD), U1.F2 (AVDD), U2.5 (OUT)
+3V3: C22.1, FB1.1, J1.12
/ADDR0: A0.2 (C), U1.C6 (ADDR0/~SS)
/ADDR1: A1.2 (C), U1.C7 (ADDR1/MOSI)
/AIN0: C17.2, U1.F6 (AIN0)
/AIN1: C18.2, U1.E5 (AIN1)
/AIN2: C16.2, U1.F5 (AIN2)
/AIN3: C19.2, U1.E4 (AIN3)
/BCLK_0: J1.3, U1.A2 (BCLK_0/MP1)
/CM: C10.1, C11.1, U1.F4 (CM)
/DVDD: C8.1, C9.1, U1.A3 (DVDD)
/FSYNC_0: J1.5, U1.B2 (FSYNC_0/MP0)
/HPOUTN0: C23.1, J3.2, R20.2, R23.1
/HPOUTN0_A: R20.1, U1.F1 (HPOUTN0/LOUTN0)
/HPOUTP0: C24.1, J3.1, R19.2, R23.2
/HPOUTP0_A: R19.1, U1.E2 (HPOUTP0/LOUTP0)
/LDO_IN: C20.1, FB1.2, U2.1 (IN), U2.3 (EN)
/MIC0_IN: C17.1, J5.2, R8.1
/MIC1_IN: C18.1, J6.1, R9.1
/MIC2_IN: C16.1, J3.4, R7.1
/MIC3_IN: C19.1, J6.5, R10.1
/MICBIAS0: C12.1, J3.6, U1.D7 (MICBIAS0)
/MICBIAS1: C13.1, J5.4, J6.3, U1.E6 (MICBIAS1)
/PD_N: J1.10, R6.2, U1.D4 (~PD)
/SCL: J1.1, R2.2, U1.B7 (SCL/SCLK)
/SDA: J1.2, R1.2, U1.B6 (SDA/MISO)
/SDATAI_0: J1.8, U1.B1 (SDATAI_0/MP2)
/SDATAO_0: R18.1, U1.A1 (SDATAO_0)
/SDATAO_0_J: J1.7, R18.2
/SELFBOOT: R5.1, U1.D6 (SELFBOOT/MP11)
/XTALI: C14.1, U1.A7 (XTALI/MCLKIN), Y1.1
/XTALO: C15.1, U1.A6 (XTALO), Y1.3
GND: A0.3 (B), A1.3 (B), C1.2, C2.2, C3.2, C4.2, C5.2, C8.2, C9.2, C10.2, C11.2, C12.2, C13.2, C14.2, C15.2, C20.2, C21.2, C22.2, C23.2, C24.2, J1.4, J1.6, J1.9, J1.11, J3.3, J3.5, J5.1, J5.3, J6.2, J6.4, J6.6, R5.2, R7.2, R8.2, R9.2, R10.2, U1.A4 (DGND), U1.D3 (SW_EN/MP12), U1.E1 (HPGND), U1.F3 (AGND), U1.F7 (AGND), U2.2 (GND), Y1.2 (G), Y1.4 (G)

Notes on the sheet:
I2C ADDRESS (7-bit): hard-wired. Populate ONE 10K resistor per address bit. ADDR1 ADDR0 : address 0 0 : 0x28 0 1 : 0x29 1 0 : 0x2A 1 1 : 0x2B
24.576 MHz, CL = 12 pF
POWER: J1 supplies +3V3 only. U2 (TLV75518, 1.8V) feeds AVDD, HPVDD, IOVDD and REG_EN (all +1V8). Digital I/O (I2C, I2S, PD_N) is 1.8V logic - NOT 3.3V tolerant. I2C pull-ups R1/R2 (4.7k) go to +1V8 from U2. Remove R1/R2 if the host provides its own pull-ups. SELFBOOT is hard-wired low by R5 (no EE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

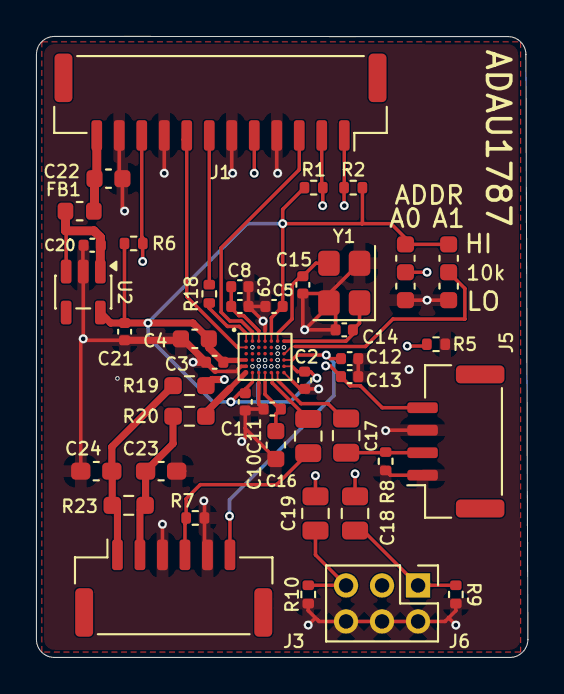
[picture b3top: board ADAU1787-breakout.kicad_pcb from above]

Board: 4 copper layers, 27.3 x 34.5 mm, 44 parts (0 on the bottom side), 33 nets.

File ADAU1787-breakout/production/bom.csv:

Designator,Footprint,Quantity,Value,LCSC Part #
"C1, C11, C2, C3, C5, C9",0402,6,100nF,C1525
"C10, C22, C4",0603,3,10uF,C2959727
"C12, C13, C20, C8",0402,4,1uF,C49210445
"C14, C15",0402,2,18pF,C1549
"C16, C17, C18, C19",0805,4,4.7uF X7R 10% 16V,CL21B475KOFNNNE
C21,0402,1,2.2uF,C2997286
FB1,0603,1,600R@100MHz 1A,C108301
J1,JST_GH_SM12B-GHS-TB_1x12-1MP_P1.25mm_Horizontal,1,HOST_IF,C265421
J3,JST_GH_SM06B-GHS-TB_1x06-1MP_P1.25mm_Horizontal,1,FB_MIC_SPK,C133065
J5,JST_GH_SM04B-GHS-TB_1x04-1MP_P1.25mm_Horizontal,1,FF_MIC,C189895
"R1, R2",0402,2,4.7k,C25900
"R10, R7, R8, R9",0402,4,49.9k,C25897
R18,0402,1,47,C25118
"R19, R20",0603,2,0R / ferrite,C21189
"R5, R6",0402,2,10k,C25744
U1,WLCSP-42_2.695x2.320mm_P0.35mm,1,ADAU1787BCBZ,C3226201
U2,SOT-23-5,1,TLV75518PDBV,C2877863
Y1,Crystal_SMD_3225-4Pin_3.2x2.5mm,1,SX32Y024576DC1T001,C20612976
